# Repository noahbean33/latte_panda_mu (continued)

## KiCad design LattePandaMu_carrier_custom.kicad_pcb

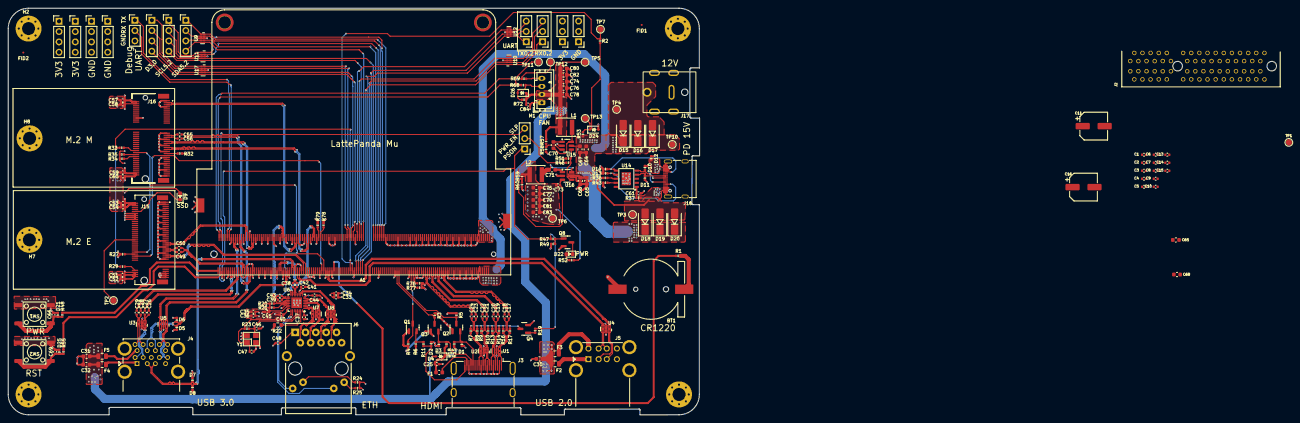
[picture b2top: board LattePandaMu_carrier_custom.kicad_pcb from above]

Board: 4 copper layers, 170.1 x 100.0 mm, 236 parts (0 on the bottom side), 198 nets.

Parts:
A1: LattePanda_Mu; LattePanda_Module_H8.0mm_Horizontal
BT1: Battery_Cell; Battery_Holder_CR1220_S8411-45R
C1, C2, C3, C4, C5, C6, C7, C8, C49, C50, C55, C56: 220nF/50V; C_0402_1005Metric
C9, C10, C13, C15, C17, C18, C19, C20, C21, C22, C23, C24, C25, C26, C27, C28, C29, C33, C34, C35, C36, C37, C38, C39, C40, C41, C42, C43, C45, C48, C52, C54, C58, C60, C84: 100nF/50V; C_0402_1005Metric
C11: 100uF/25V; CP_Elec_6.3x7.7
C14: 10uF/10V; C_0402_1005Metric
C16: 560uF/25V; CP_Elec_6.3x7.7
C30, C31, C32, C64, C65, C65#2, C67, C68, C68#2, C74, C75, C76, C77, C80, C81, C82, C83: 22uF/10V; C_0603_1608Metric
C44, C51, C53, C57, C59: 10uF/50V; C_0402_1005Metric
C46, C47, C73: 12pF/50V; C_0402_1005Metric
C61, C66, C69: 1uF/16V; C_0402_1005Metric
C70, C71: 100nF/50V; C_0603_1608Metric
C78, C79: 100nF/10V; C_0603_1608Metric
D1, D2, D3: ESD5V0B03; D_0402_1005Metric
D4, D26: 1N5819WS; D_SOD-323
D5, D6, D7, D8, D10, D11, D21, D25: ESD9B5.0ST5G; D_0402_1005Metric
D9: LED_G; LED_0603_1608Metric
D12, D13, D14: D_Zener; D_0402_1005Metric
D15, D16, D17, D18, D19, D20: D_Schottky; D_SMA
D22: LED; LED_0603_1608Metric
D24: 3V3 Izt=5mA; D_SOD-323
F1: 6V/50mA; C_0603_1608Metric
F2, F3, F4, F5: 6V/1A; Fuse_0805_2012Metric
FID1, FID2: Fiducial; Fiducial_0.5mm_Mask1mm
H1, H2, H3, H4, H7, H8: MountingHole_Pad; MountingHole_3.2mm_M3_Pad_Via
H5, H6: MountingHole_Pad; MountingHole_3mm_M2_Pad_TopOnly
J1, J8, J10, J11, J14: Conn_01x03_Pin; PinHeader_1x03_P2.54mm_Vertical
J2: Bus_PCI_Express_x4; PCIe_x4_Gen3Slot_Connectors
J3: HDMI_A; HDMI_A_Molex_208658-1001_Horizontal
J4: USB3_A_Stacked; USB3_A_Molex_48406-0001_Horizontal_Stacked
J5: USB_A_Stacked; USB_A_CUI_UJ2-ADH-TH_Horizontal_Stacked
J6: RJ45_RB1-125B8G1A; RJ45_UDE_RB1-125B8G1A
J7, J9, J12, J13, J19, J20, J21: Conn_01x04_Pin; PinHeader_1x04_P2.54mm_Vertical
J15: Bus_M.2_Socket_M; PCIe_M.2_Connectors_P=0.5mm_H=4.2mm_KeyM
J16: Bus_M.2_Socket_E; PCIe_M.2_Connectors_P=0.5mm_H=4.2mm_KeyE
J17: Barrel_Jack_Switch; DC_Jack_DC007B_30V_10A
J18: USB_C_Receptacle_USB2.0_16P; USB_C_Receptacle_G-Switch_GT-USB-7010ASV
JP1: Jumper_3_Bridged12; PinHeader_1x03_P2.54mm_Vertical
L1, L2: 2.2uH/4.3A; L_Sunlord_SWPA4020S
M1: Fan_4pin; JST_PH_B4B-PH-K_1x04_P2.00mm_Vertical
Q1, Q8: 2N7002; SOT-23
Q2, Q3, Q4: 2SK3018; SOT-23
R1, R11, R37, R47: 1K/1%; R_0402_1005Metric
R2, R20, R21, R34, R35, R36, R49, R58, R78, R79: 10K/1%; R_0402_1005Metric
R3, R5, R15, R18, R19, R52, R53: 2.2K/1%; R_0402_1005Metric
R4, R23: 1M/1%; R_0402_1005Metric
R6, R59, R68: 21.5K/1%; R_0402_1005Metric
R7, R8, R9, R10, R13, R14, R16, R17, R24, R25: 470R/1%; R_0402_1005Metric
R22: 2.49K/1%; R_0603_1608Metric
R27, R29, R32, R33: 0R/1%; R_0402_1005Metric
R43: 56K/1%; R_0402_1005Metric
R46, R51, R76, R77: 100K/1%; R_0402_1005Metric
R48, R55, R69: 100R/1%; R_0402_1005Metric
R57: 75K/1%; R_0402_1005Metric
R60, R72: 4.7K/1%; R_0402_1005Metric
SW1, SW2: SW_Push; SW_Push_6x6x6
TP1, TP2, TP3, TP4, TP5, TP6, TP7, TP10, TP11, TP12, TP13: TestPoint; TestPoint_Pad_D1.5mm
U1, U2, U3, U4, U5, U7, U8: D3V3XA4B10LP; Diodes_UDFN-10_1.0x2.5mm_P0.5mm
U6: RTL8111H-CG-RH; QFN-32-1EP_4x4mm_P0.4mm_EP2.65x2.65mm
U9, U10, U11, U12, U17: ULC0524P; Diodes_UDFN-10_1.0x2.5mm_P0.5mm
U14: USB PD等快充协议受电芯片-CH224K-ESSOP10; ESSOP-10-1EP_3.9x5mm_P1.0mm_EP3.2x2.3
U15, U16: LM2734X; TSOT-23-6
Y1: 25MHz; Crystal_SMD_3225-4Pin_3.2x2.5mm

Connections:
5V_HDMI_VCC: C25.1, D4.1 (K), F1.1, R15.1, R18.1
+1V0: C33.2, C34.2, C35.2, C36.2, C40.2, C44.2, U6.3 (AVDD10), U6.8 (AVDD10), U6.22 (DVDD10), U6.24 (REGOUT), U6.30 (AVDD10)
+3V3: C13.2, C14.2, C15.1, C16.1, C37.2, C41.2, C45.2, C51.2, C52.2, C53.2, C54.2, C57.2, C58.2, C59.2, C60.2, C73.1, C75.1, C77.1, C79.1, C81.1, C83.1, D9.2 (A), J2.A9 (+3.3V), J2.A10 (+3.3V), J2.B8 (+3.3V), J2.B10 (3.3Vaux), J13.1, J13.2, J13.3, J13.4, J14.1, J14.2, J14.3, J15.2 (3.3V), J15.4 (3.3V), J15.12 (3.3V), J15.14 (3.3V), J15.16 (3.3V), J15.18 (3.3V), J15.70 (3.3V), J15.72 (3.3V), J15.74 (3.3V), J16.2 (3.3V), J16.4 (3.3V), J16.72 (3.3V), J16.74 (3.3V), J21.1, J21.2, J21.3, J21.4, L2.2, Q1.1 (G), Q2.1 (G), Q3.1 (G), R3.1, R4.1, R5.1, R20.2, R21.2, R24.2, R25.2, R34.2, R35.2, R52.1, R59.2, TP6.1 (1_1), U6.11 (AVDD33), U6.23 (VDDREG), U6.32 (AVDD33)
+5V: C30.2, C31.2, C32.2, C74.1, C76.1, C78.1, C80.1, C82.1, C84.1, D4.2 (A), D26.1 (K), F2.1, F3.1, F4.1, F5.1, L1.2, M1.2 (+), R57.2, R72.1, TP5.1 (1_1)
+12V: D15.2 (A), D16.2 (A), D17.2 (A), J17.1, TP4.1 (1_1)
+12VA: C9.1, C10.1, C11.1, J2.A2 (+12V), J2.A3 (+12V), J2.B1 (+12V), J2.B2 (+12V), J2.B3 (+12V)
+15V: D12.1 (K), D18.2 (A), D19.2 (A), D20.2 (A), J18.A4 (VBUS), J18.A9 (VBUS), J18.B4 (VBUS), J18.B9 (VBUS), R36.1, R37.1, TP3.1 (1_1)
+BATT: A1.115 (VBAT), R1.2
/Fan/FAN_1_PWM: A1.2 (FAN1_PWM), R69.1, TP12.1 (1_1)
/Fan/FAN_1_TAC: A1.4 (FAN1_TAC), R68.1, TP11.1 (1_1)
/GPIO/GPP_D0: A1.128 (GPP_D0), J19.1, U17.1, U17.10 (NC)
/GPIO/GPP_D1: A1.130 (GPP_D1), J19.2, U17.2, U17.9 (NC)
/GPIO/GPP_D2: A1.132 (GPP_D2), J19.3, U17.4, U17.7 (NC)
/GPIO/GPP_D3: A1.134 (GPP_D3), J19.4, U17.5, U17.6 (NC)
/GPIO/I2C2_SCL: A1.154 (I2C2_SCL), J9.1, U11.1, U11.10 (NC)
/GPIO/I2C2_SDA: A1.156 (I2C2_SDA), J7.1, U9.1, U9.10 (NC)
/GPIO/I2C3_SCL: A1.150 (I2C3_SCL), J9.2, U11.2, U11.9 (NC)
/GPIO/I2C3_SDA: A1.152 (I2C3_SDA), J7.2, U9.2, U9.9 (NC)
/GPIO/I2C4_SCL: A1.146 (I2C4_SCL), J9.3, U11.4, U11.7 (NC)
/GPIO/I2C4_SDA: A1.148 (I2C4_SDA), J7.3, U9.4, U9.7 (NC)
/GPIO/I2C5_SCL: A1.142 (I2C5_SCL), J9.4, U11.5, U11.6 (NC)
/GPIO/I2C5_SDA: A1.144 (I2C5_SDA), J7.4, U9.5, U9.6 (NC)
/GPIO/SOC_UART0_RX: A1.137 (UART0_RXD), J8.1, U10.1, U10.10 (NC)
/GPIO/SOC_UART0_TX: A1.139 (UART0_TXD), J10.1, U12.1, U12.10 (NC)
/GPIO/SOC_UART1_RX: A1.141 (UART1_RXD), J8.2, U10.2, U10.9 (NC)
/GPIO/SOC_UART1_TX: A1.143 (UART1_TXD), J10.2, U12.2, U12.9 (NC)
/GPIO/SOC_UART2_RX: A1.140 (UART2_RXD), J8.3, U10.4, U10.7 (NC)
/GPIO/SOC_UART2_TX: A1.138 (UART2_TXD), J10.3, U12.4, U12.7 (NC)
/Gigabit Ethernet/GbE_PCIe_CLK+: A1.94 (REFCLK4+), U6.15 (REFCLK_P)
/Gigabit Ethernet/GbE_PCIe_CLK-: A1.96 (REFCLK4-), U6.16 (REFCLK_N)
/Gigabit Ethernet/GbE_PCIe_RX+: A1.64 (HSIO6_RX+), C43.2
/Gigabit Ethernet/GbE_PCIe_RX-: A1.66 (HSIO6_RX-), C39.2
/Gigabit Ethernet/GbE_PCIe_TX+: A1.61 (HSIO6_TX+), C42.2
/Gigabit Ethernet/GbE_PCIe_TX-: A1.63 (HSIO6_TX-), C38.2
/Gigabit Ethernet/HSI+: C42.1, U6.13 (HSIP)
/Gigabit Ethernet/HSI-: C38.1, U6.14 (HSIN)
/Gigabit Ethernet/HSO+: C43.1, U6.17 (HSOP)
/Gigabit Ethernet/HSO-: C39.1, U6.18 (HSON)
/Gigabit Ethernet/MDI0+: J6.R2 (TD1+), U6.1 (MDIP0), U7.1, U7.10 (NC)
/Gigabit Ethernet/MDI0-: J6.R3 (TD1-), U6.2 (MDIN0), U7.2, U7.9 (NC)
/Gigabit Ethernet/MDI1+: J6.R4 (TD2+), U6.4 (MDIP1), U7.4, U7.7 (NC)
/Gigabit Ethernet/MDI1-: J6.R5 (TD2-), U6.5 (MDIN1), U7.5, U7.6 (NC)
/Gigabit Ethernet/MDI2+: J6.R6 (TD3+), U6.6 (MDIP2), U8.5, U8.6 (NC)
/Gigabit Ethernet/MDI2-: J6.R7 (TD3-), U6.7 (MDIN2), U8.4, U8.7 (NC)
/Gigabit Ethernet/MDI3+: J6.R8 (TD4+), U6.9 (MDIP3), U8.2, U8.9 (NC)
/Gigabit Ethernet/MDI3-: J6.R9 (TD4-), U6.10 (MDIN3), U8.1, U8.10 (NC)
/HDMI/DDC_SCL: D1.2 (A2), J3.15 (SCL), Q2.2 (S), R15.2
/HDMI/DDC_SDA: D3.2 (A2), J3.16 (SDA), Q3.2 (S), R18.2
/HDMI/DDI_B_DDC_SCL: A1.171 (DDIB_DDC_SCL), Q2.3 (D), R5.2
/HDMI/DDI_B_DDC_SDA: A1.169 (DDIB_DDC_SDA), Q3.3 (D), R3.2
/HDMI/DDI_B_HPD: A1.183 (DDIB_HPD), Q1.3 (D), R4.2
/HDMI/DDI_B_TX0+: A1.217 (DDIB_TX0+), C17.1
/HDMI/DDI_B_TX0-: A1.215 (DDIB_TX0-), C18.1
/HDMI/DDI_B_TX1+: A1.211 (DDIB_TX1+), C19.1
/HDMI/DDI_B_TX1-: A1.209 (DDIB_TX1-), C20.1
/HDMI/DDI_B_TX2+: A1.205 (DDIB_TX2+), C21.1
/HDMI/DDI_B_TX2-: A1.203 (DDIB_TX2-), C22.1
/HDMI/DDI_B_TX3+: A1.199 (DDIB_TX3+), C23.1
/HDMI/DDI_B_TX3-: A1.197 (DDIB_TX3-), C24.1
/HDMI/HPD: D2.2 (A2), J3.19 (HPD), R11.2
/HDMI/TMDS_CK+: C23.2, J3.10 (CK+), R8.2, U2.4, U2.7 (NC)
/HDMI/TMDS_CK-: C24.2, J3.12 (CK-), R7.2, U2.5, U2.6 (NC)
/HDMI/TMDS_D0+: C21.2, J3.7 (D0+), R10.2, U2.1, U2.10 (NC)
/HDMI/TMDS_D0-: C22.2, J3.9 (D0-), R9.2, U2.2, U2.9 (NC)
/HDMI/TMDS_D1+: C19.2, J3.4 (D1+), R14.2, U1.4, U1.7 (NC)
/HDMI/TMDS_D1-: C20.2, J3.6 (D1-), R13.2, U1.5, U1.6 (NC)
/HDMI/TMDS_D2+: C17.2, J3.1 (D2+), R17.2, U1.1, U1.10 (NC)
/HDMI/TMDS_D2-: C18.2, J3.3 (D2-), R16.2, U1.2, U1.9 (NC)
/LattePanda Module/HSIO_0_TX+: A1.13 (HSIO0_TX+), C27.1
/LattePanda Module/HSIO_0_TX-: A1.15 (HSIO0_TX-), C26.1
/LattePanda Module/HSIO_1_TX+: A1.19 (HSIO1_TX+), C29.1
/LattePanda Module/HSIO_1_TX-: A1.21 (HSIO1_TX-), C28.1
/LattePanda Module/HSIO_2_RX+: A1.28 (HSIO2_RX+), J15.43 (PERp0/SATA-B-)
/LattePanda Module/HSIO_2_RX-: A1.30 (HSIO2_RX-), J15.41 (PERn0/SATA-B+)
/LattePanda Module/HSIO_2_TX+: A1.25 (HSIO2_TX+), C49.1
/LattePanda Module/HSIO_2_TX-: A1.27 (HSIO2_TX-), C50.1
/LattePanda Module/HSIO_3_RX+: A1.34 (HSIO3_RX+), J16.41 (PERp0)
/LattePanda Module/HSIO_3_RX-: A1.36 (HSIO3_RX-), J16.43 (PERn0)
/LattePanda Module/HSIO_3_TX+: A1.31 (HSIO3_TX+), C55.1
/LattePanda Module/HSIO_3_TX-: A1.33 (HSIO3_TX-), C56.1
/LattePanda Module/HSIO_8_RX+: A1.40 (HSIO8_RX+), J2.A16 (PERp0)
/LattePanda Module/HSIO_8_RX-: A1.42 (HSIO8_RX-), J2.A17 (PERn0)
/LattePanda Module/HSIO_8_TX+: A1.37 (HSIO8_TX+), C1.1
/LattePanda Module/HSIO_8_TX-: A1.39 (HSIO8_TX-), C2.1
/LattePanda Module/HSIO_9_RX+: A1.46 (HSIO9_RX+), J2.A21 (PERp1)
/LattePanda Module/HSIO_9_RX-: A1.48 (HSIO9_RX-), J2.A22 (PERn1)
/LattePanda Module/HSIO_9_TX+: A1.43 (HSIO9_TX+), C3.1
/LattePanda Module/HSIO_9_TX-: A1.45 (HSIO9_TX-), C4.1
/LattePanda Module/HSIO_10_RX+: A1.52 (HSIO10_RX+), J2.A25 (PERp2)
/LattePanda Module/HSIO_10_RX-: A1.54 (HSIO10_RX-), J2.A26 (PERn2)
/LattePanda Module/HSIO_10_TX+: A1.49 (HSIO10_TX+), C5.1
/LattePanda Module/HSIO_10_TX-: A1.51 (HSIO10_TX-), C6.1
/LattePanda Module/HSIO_11_RX+: A1.58 (HSIO11_RX+), J2.A29 (PERp3)
/LattePanda Module/HSIO_11_RX-: A1.60 (HSIO11_RX-), J2.A30 (PERn3)
/LattePanda Module/HSIO_11_TX+: A1.55 (HSIO11_TX+), C7.1
/LattePanda Module/HSIO_11_TX-: A1.57 (HSIO11_TX-), C8.1
/LattePanda Module/REFCLK0+: A1.85 (REFCLK0+), J15.55 (REFCLKp)
/LattePanda Module/REFCLK0-: A1.87 (REFCLK0-), J15.53 (REFCLKn)
/LattePanda Module/REFCLK2+: A1.97 (REFCLK2+), J2.A13 (REFCLK+)
/LattePanda Module/REFCLK2-: A1.99 (REFCLK2-), J2.A14 (REFCLK-)
/LattePanda Module/REFCLK3+: A1.88 (REFCLK3+), J16.47 (REFCLKp0)
/LattePanda Module/REFCLK3-: A1.90 (REFCLK3-), J16.49 (REFCLKn0)
/LattePanda Module/SUSCKL_WIFI: A1.131 (SUSCLK), R29.1, R33.2
/LattePanda Module/USB_2_P7+: A1.76 (USB2_P7+), J16.3 (USB_D+)
/LattePanda Module/USB_2_P7-: A1.78 (USB2_P7-), J16.5 (USB_D-)
/LattePanda Module/~PWR_SW: A1.1 (~PWRBTN), R48.1
/LattePanda Module/~RST_SW: A1.3 (~RSTBTN), R55.1
/M.2 M Key/CON_PCIE_TX0+: C55.2, J16.35 (PETp0)
/M.2 M Key/CON_PCIE_TX0-: C56.2, J16.37 (PETn0)
/M.2 M Key/CON_PCIE_TX1+: C49.2, J15.49 (PETp0/SATA-A+)
/M.2 M Key/CON_PCIE_TX1-: C50.2, J15.47 (PETn0/SATA-A-)
/M.2 M Key/~CLKREQE: J16.53 (~CLKREQ0), R32.1
/M.2 M Key/~CLKREQM: J15.52 (~CLKREQ), R27.1
/PCIe x4/PCIE30_TX0_N: C2.2, J2.B15 (PETn0)
/PCIe x4/PCIE30_TX0_P: C1.2, J2.B14 (PETp0)
/PCIe x4/PCIE30_TX1_N: C4.2, J2.B20 (PETn1)
/PCIe x4/PCIE30_TX1_P: C3.2, J2.B19 (PETp1)
/PCIe x4/PCIE30_TX2_N: C6.2, J2.B24 (PETn2)
/PCIe x4/PCIE30_TX2_P: C5.2, J2.B23 (PETp2)
/PCIe x4/PCIE30_TX3_N: C8.2, J2.B28 (PETn3)
/PCIe x4/PCIE30_TX3_P: C7.2, J2.B27 (PETp3)
/Power Supply/CC1: D13.1 (K), J18.A5 (CC1), U14.7 (CC1)
/Power Supply/CC2: D14.1 (K), J18.B5 (CC2), U14.6 (CC2)
/Power Supply/PWR_C_D+: D11.2 (A2), J18.A6 (D+), J18.B6 (D+), U14.4 (DP)
/Power Supply/PWR_C_D-: D10.2 (A2), J18.A7 (D-), J18.B7 (D-), U14.5 (DM)
/Power Supply/PWR_EN: R46.1, R51.2, U15.4 (EN), U16.4 (EN)
/USB 2.0 & 3.0/CON_USB1_D_N: A1.109 (USB2_P5-), J5.2 (D1-), U4.2, U4.9 (NC)
/USB 2.0 & 3.0/CON_USB1_D_P: A1.111 (USB2_P5+), J5.3 (D1+), U4.1, U4.10 (NC)
/USB 2.0 & 3.0/CON_USB2_D_N: A1.79 (USB2_P3-), J5.6 (D2-), U4.5, U4.6 (NC)
/USB 2.0 & 3.0/CON_USB2_D_P: A1.81 (USB2_P3+), J5.7 (D2+), U4.4, U4.7 (NC)
/USB 2.0 & 3.0/CON_USB3_D_N: A1.73 (USB2_P2-), D8.1 (A1), J4.2 (D1-)
/USB 2.0 & 3.0/CON_USB3_D_P: A1.75 (USB2_P2+), D7.1 (A1), J4.3 (D1+)
/USB 2.0 & 3.0/CON_USB3_SSRX_N: A1.18 (HSIO0_RX-), J4.5 (SSRX1-), U5.4, U5.7 (NC)
/USB 2.0 & 3.0/CON_USB3_SSRX_P: A1.16 (HSIO0_RX+), J4.6 (SSRX1+), U5.5, U5.6 (NC)
/USB 2.0 & 3.0/CON_USB3_SSTX_N: C26.2, J4.8 (SSTX1-), U3.1, U3.10 (NC)
/USB 2.0 & 3.0/CON_USB3_SSTX_P: C27.2, J4.9 (SSTX1+), U3.2, U3.9 (NC)
/USB 2.0 & 3.0/CON_USB4_D_N: A1.67 (USB2_P1-), D6.1 (A1), J4.11 (D2-)
/USB 2.0 & 3.0/CON_USB4_D_P: A1.69 (USB2_P1+), D5.1 (A1), J4.12 (D2+)
/USB 2.0 & 3.0/CON_USB4_SSRX_N: A1.24 (HSIO1_RX-), J4.14 (SSRX2-), U5.1, U5.10 (NC)
/USB 2.0 & 3.0/CON_USB4_SSRX_P: A1.22 (HSIO1_RX+), J4.15 (SSRX2+), U5.2, U5.9 (NC)
/USB 2.0 & 3.0/CON_USB4_SSTX_N: C28.2, J4.17 (SSTX2-), U3.4, U3.7 (NC)
/USB 2.0 & 3.0/CON_USB4_SSTX_P: C29.2, J4.18 (SSTX2+), U3.5, U3.6 (NC)
/~PLT_RST: A1.105 (~PLTRST), J2.A11 (~PERST), J15.50 (~PERST), J16.52 (~PERST0), TP1.1 (1_1), U6.19 (PERSTB)
/~PWR_LED/~PSON: A1.5 (SLS_S0), JP1.1 (A), R19.1, R47.2
/~WAKE: A1.103 (~WAKE), J2.B11 (~WAKE), J15.54 (~PEWAKE), J16.55 (~PEWAKE0)
GND: A1.11 (GND), A1.14 (GND), A1.17 (GND), A1.20 (GND), A1.23 (GND), A1.26 (GND), A1.29 (GND), A1.32 (GND), A1.35 (GND), A1.38 (GND), A1.41 (GND), A1.44 (GND), A1.47 (GND), A1.50 (GND), A1.53 (GND), A1.56 (GND), A1.59 (GND), A1.62 (GND), A1.65 (GND), A1.68 (GND), A1.71 (GND), A1.74 (GND), A1.77 (GND), A1.80 (GND), A1.83 (GND), A1.86 (GND), A1.89 (GND), A1.92 (GND), A1.95 (GND), A1.98 (GND), A1.101 (GND), A1.107 (GND), A1.110 (GND), A1.113 (GND), A1.116 (GND), A1.135 (GND), A1.136 (GND), A1.151 (GND), A1.158 (GND), A1.167 (GND), A1.170 (GND), A1.181 (GND), A1.182 (GND), A1.188 (GND), A1.189 (GND), A1.194 (GND), A1.195 (GND), A1.200 (GND), A1.201 (GND), A1.206 (GND), A1.207 (GND), A1.212 (GND), A1.213 (GND), A1.218 (GND), A1.219 (GND), A1.224 (GND), A1.225 (GND), A1.230 (GND), A1.231 (GND), A1.236 (GND), A1.237 (GND), A1.242 (GND), A1.243 (GND), A1.248 (GND), A1.249 (GND), A1.MP (Mountinge_Pads), BT1.2 (-), C9.2, C10.2, C11.2, C13.1, C14.1, C15.2, C16.2, C25.2, C30.1, C31.1, C32.1, C33.1, C34.1, C35.1, C36.1, C37.1, C40.1, C41.1, C44.1, C45.1, C46.2, C47.2, C48.1, C51.1, C52.1, C53.1, C54.1, C57.1, C58.1, C59.1, C60.1, C61.1, C64.1, C65.2, C65#2.1, C66.2, C67.1, C68.1, C68#2.2, C69.2, C74.2, C75.2, C76.2, C77.2, C78.2, C79.2, C80.2, C81.2, C82.2, C83.2, C84.2, D1.1 (A1), D2.1 (A1), D3.1 (A1), D5.2 (A2), D6.2 (A2), D7.2 (A2), D8.2 (A2), D10.1 (A1), D11.1 (A1), D12.2 (A), D13.2 (A), D14.2 (A), D21.2 (A2), D24.2 (A), D25.2 (A2), H1.1 (1_1), H2.1 (1_1), H3.1 (1_1), H4.1 (1_1), H5.1 (1_1), H6.1 (1_1), H7.1 (1_1), H8.1 (1_1), J1.3, J2.A1 (~PRSNT1), J2.A4 (GND), J2.A12 (GND), J2.A15 (GND), J2.A18 (GND), J2.A20 (GND), J2.A23 (GND), J2.A24 (GND), J2.A27 (GND), J2.A28 (GND), J2.A31 (GND), J2.B4 (GND), J2.B7 (GND), J2.B13 (GND), J2.B16 (GND), J2.B17 (~PRSNT2), J2.B18 (GND), J2.B21 (GND), J2.B22 (GND), J2.B25 (GND), J2.B26 (GND), J2.B29 (GND), J2.B31 (~PRSNT2), J2.B32 (GND), J3.2 (D2S), J3.5 (D1S), J3.8 (D0S), J3.11 (CKS), J3.17 (GND), J3.SH, J4.4 (GND1), J4.7 (DRAIN1), J4.13 (GND2), J4.16 (DRAIN2), J4.19 (SHIELD), J5.4 (GND1), J5.8 (GND2), J5.9 (Shield), J6.R10 (GND), J6.SH, J11.1, J11.2, J11.3, J12.1, J12.2, J12.3, J12.4, J15.1 (GND), J15.3 (GND), J15.9 (GND), J15.15 (GND), J15.21 (GND), J15.27 (GND), J15.33 (GND), J15.39 (GND), J15.45 (GND), J15.51 (GND), J15.57 (GND), J15.71 (GND), J15.73 (GND), J15.75 (GND), J16.1 (GND), J16.7 (GND), J16.18 (GND), J16.33 (GND), J16.39 (GND), J16.45 (GND), J16.51 (GND), J16.57 (GND), J16.63 (GND), J16.69 (GND), J16.75 (GND), J17.2, J17.3, J18.A1 (GND), J18.A12 (GND), J18.B1 (GND), J18.B12 (GND), J18.S1 (SHIELD), J20.1, J20.2, J20.3, J20.4, M1.1 (-), Q4.2 (S), Q8.2 (S), R6.2, R22.2, R27.2, R32.2, R43.2, R49.2, R51.1, R58.1, R60.1, R76.2, R77.2, R78.1, R79.1, SW1.2, SW2.2, U1.3 (VSS), U1.8 (VSS), U2.3 (VSS), U2.8 (VSS), U3.3 (VSS), U3.8 (VSS), U4.3 (VSS), U4.8 (VSS), U5.3 (VSS), U5.8 (VSS), U6.33 (GND), U7.3 (VSS), U7.8 (VSS), U8.3 (VSS), U8.8 (VSS), U9.3 (VSS), U9.8 (VSS), U10.3 (VSS), U10.8 (VSS), U11.3 (VSS), U11.8 (VSS), U12.3 (VSS), U12.8 (VSS), U14.0 (GND), U15.2 (GND), U16.2 (GND), U17.3 (VSS), U17.8 (VSS), Y1.2, Y1.4
unnamed: A1.12 (SIO_UART_RX), J1.2
unnamed: A1.10 (SIO_UART_TX), J1.1
unnamed: A1.187 (TCP0_HPD), R76.1
unnamed: A1.185 (TCP1_HPD), R77.1
unnamed: A1.133 (~BIOS_SEL), R2.1, TP7.1 (1_1)
unnamed: A1.100 (~CLKREQ3), R79.2
unnamed: A1.102 (~CLKREQ4), R78.2
unnamed: BT1.1 (+), R1.1
unnamed: D9.1 (K), J15.10 (DAS/~DSS/~LED1)
unnamed: C66.1, D21.1 (A1), R48.2, SW1.1
unnamed: D22.2 (A), R52.2
unnamed: D22.1 (K), Q8.3 (D)
unnamed: C69.1, D25.1 (A1), R55.2, SW2.1
unnamed: D26.2 (A), M1.3 (Tacho), R68.2, R72.2
unnamed: F1.2, J3.18 (+5V)
unnamed: F4.2, J4.1 (VBUS1)
unnamed: F5.2, J4.10 (VBUS2)
unnamed: F2.2, J5.1 (VBUS1)
unnamed: F3.2, J5.5 (VBUS2)
unnamed: C48.2, J6.R1 (CT)
unnamed: J6.L1, R25.1
unnamed: J6.L3, R24.1
unnamed: J15.38 (DEVSLP), TP2.1 (1_1)
unnamed: J15.68 (SUSCLK), R29.2
unnamed: J16.50 (SUSCLK), R33.1
unnamed: J16.56 (~W_DISABLE1), R34.1
unnamed: J16.54 (~W_DISABLE2), R35.1
unnamed: M1.4 (PWM), R69.2
unnamed: Q1.2 (S), R6.1, R11.1
unnamed: Q4.3 (D), R7.1, R8.1, R9.1, R10.1, R13.1, R14.1, R16.1, R17.1
unnamed: Q4.1 (G), R19.2
unnamed: Q8.1 (G), R47.1, R49.1
unnamed: C47.1, R23.1, U6.28 (CKXTAL1), Y1.1
unnamed: C46.1, R23.2, U6.29 (CKXTAL2), Y1.3
unnamed: R20.1, U6.20 (ISOLATEB)
unnamed: R21.1, U6.21 (LANWAKEB)
unnamed: J6.L4, U6.26 (LED1)
unnamed: J6.L2, U6.25 (LED2)
unnamed: R22.1, U6.31 (RSET)
unnamed: U10.5, U10.6 (NC)
unnamed: U12.5, U12.6 (NC)
unnamed: R43.1, U14.9 (CFG1)
unnamed: R36.2, U14.8 (VBUS)
unnamed: C61.2, R37.2, U14.1 (VDD)
unnamed: C70.2, U15.1 (BOOST)
unnamed: R57.1, R58.2, U15.3 (FB)
unnamed: C70.1, L1.1, U15.6 (SW)
unnamed: C71.2, U16.1 (BOOST)
unnamed: C73.2, R59.1, R60.2, U16.3 (FB)
unnamed: C71.1, L2.1, U16.6 (SW)
VDC: A1.7 (SLS_S3), A1.250 (VIN), A1.251 (VIN), A1.252 (VIN), A1.253 (VIN), A1.254 (VIN), A1.255 (VIN), A1.256 (VIN), A1.257 (VIN), A1.258 (VIN), A1.259 (VIN), A1.260 (VIN), C64.2, C65.1, C65#2.2, C67.2, C68.2, C68#2.1, D15.1 (K), D16.1 (K), D17.1 (K), D18.1 (K), D19.1 (K), D20.1 (K), JP1.2 (C), JP1.3 (B), R46.2, R53.2, TP10.1 (1_1), U15.5 (VIN), U16.5 (VIN)
VPullup: D24.1 (K), R2.2, R53.1, TP13.1 (1_1)

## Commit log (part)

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2025-12-07 added vendor information
